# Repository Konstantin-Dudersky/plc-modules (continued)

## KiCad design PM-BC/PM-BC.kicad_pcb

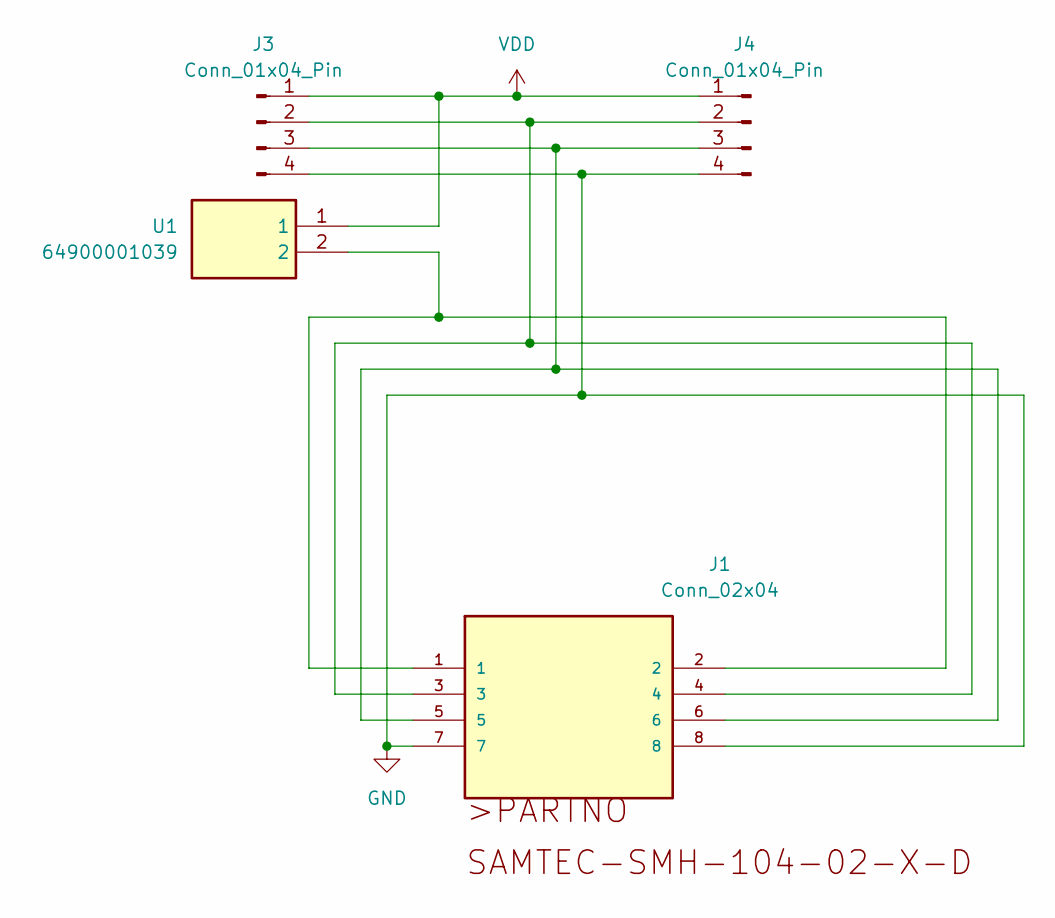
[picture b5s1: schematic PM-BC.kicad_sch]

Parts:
J1: Conn_02x04; Conn_02x04_socket_angle
J3, J4: Conn_01x04_Pin; PinHeader_1x04_P2.54mm_Vertical_SMD_Pin1Left
U1: 64900001039; Fuseholder; Manufacturer_Part_Number 64900001039; Mouser Part Number 576-64900001039

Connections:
GND: J1.7, J1.8, J3.4, J4.4
unnamed: J1.1, J1.2, U1.2
unnamed: J1.3, J1.4, J3.2, J4.2
unnamed: J1.5, J1.6, J3.3, J4.3
VDD: J3.1, J4.1, U1.1

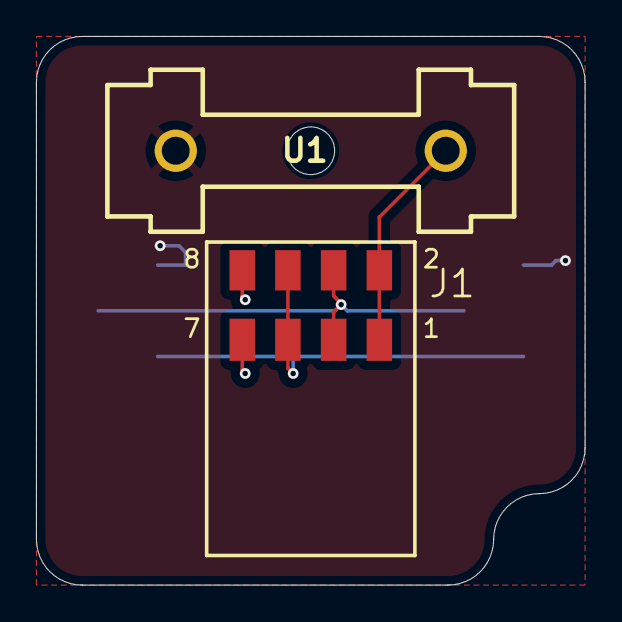
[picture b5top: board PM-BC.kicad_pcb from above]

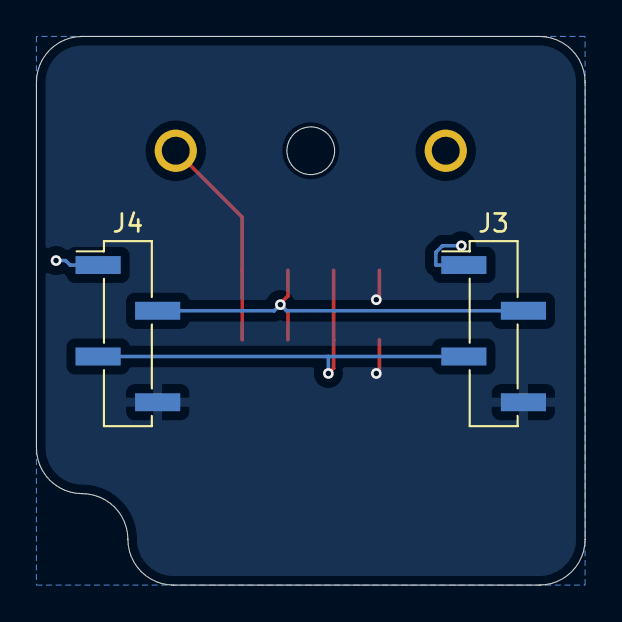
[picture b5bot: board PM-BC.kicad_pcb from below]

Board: 2 copper layers, 30.5 x 30.5 mm, 4 parts (2 on the bottom side), 5 nets.

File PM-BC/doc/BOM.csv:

Reference,Value,Footprint,Qty,NextPCB_price,NextPCB_url
J1,Conn_02x04,NextPCB:Conn_02x04_socket_angle,1,0.20095,https://www.hqonline.com/product-detail/female-headers-hctl-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
"J3,J4",Conn_01x04_Pin,Connector_PinHeader_2.54mm:PinHeader_1x04_P2.54mm_Vertical_SMD_Pin1Left,2,,
U1,64900001039,NextPCB:Fuseholder,1,0.4163,https://www.hqonline.com/product-detail/fuse-holders---clips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
